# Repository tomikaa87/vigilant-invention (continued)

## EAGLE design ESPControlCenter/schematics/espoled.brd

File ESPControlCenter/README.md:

# ESP Control Center

ESP Control Center is a multifunctional unit for monitoring and interacting with
smart home equipment (like a thermostat, AC units, home server etc.).

## Hardware components

- ESP12E module [[AliExpress](https://www.aliexpress.com/item/1PCS-ESP-12F-ESP-12E-upgrade-ESP8266-Remote-Serial-Port-WIFI-Wireless-Module/32714088769.html)]
- SSD1306-based OLED display [[AliExpress](https://www.aliexpress.com/item/1pcs-Free-Shipping-White-Blue-White-and-Blue-color-0-96-inch-128X64-OLED-Display-Module/32717950155.html)]
- Push buttons
- *TODO: power supply, battery management*
 - https://www.aliexpress.com/item/DD0603SA-3V3-Auto-Buck-Boost-DC-DC-0-9-6V-to-3-3V-Step-UP-Step/32787898065.html
 - https://www.aliexpress.com/item/0-7-5V-to-3V-3-3V-5V-DC-DC-Boost-Converter-voltage-Step-up-Module/32800430445.html

## Software components

### u8g2 graphics library

#### Custom fonts from TTF

1. Download `otf2bdf` from [rtfreesoft](http://rtfreesoft.blogspot.hu/2014/12/otf2bdf-self-forked.html)
1. Download `bdfconv` from [u8g2's GitHub](https://github.com/olikraus/u8g2/blob/master/tools/font/bdfconv/bdfconv.exe)
1. (optional) Download `Chortkeh BDF Font Viewer` from [Chortkeh](http://www.chortkeh.com/font-toolbox/bdf-font-viewer) if you want to
see the contents of the generated BDF file on Windows
1. Generate a BDF file from the TTF font of your choice by running this command:
`otf2bdf.exe -r 72 -p 32 "c:\Work\ultimate_oldschool_pc_font_pack_v1.0\PxPlus (TrueType - extended charset)\PxPlus_IBM_VGA8.ttf" -o c:\Work\pxplus-vga8-32.bdf`
1. (optional) Check the result with `Chortkeh BDF Font Viewer` and see the character codes you want to encode in the next step
1. Convert the BDF file to u8g2's binary format via `bdfconv.exe -v -f 1 -m "32,48-57" ..\pxplus-vga8-32.bdf -o ..\pxplus-vga8-32.c -n pxplus_vga8_32_nums -d ..\pxplus-vga8-32.bdf`

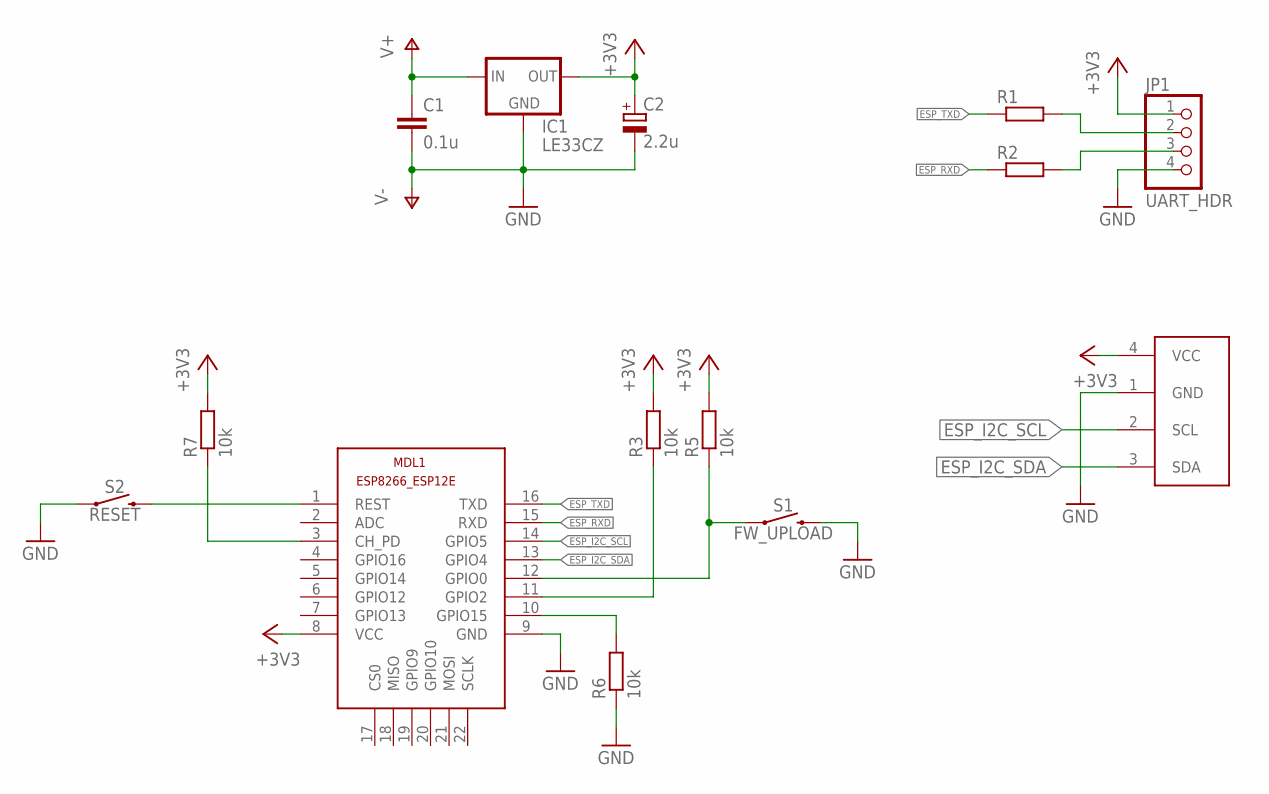
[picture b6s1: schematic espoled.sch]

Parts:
C1: 0.1u; C025-024X044
C2: 2.2u; E2,5-5
IC1: LE33CZ; TO92
JP1: UART_HDR; 1X04
MDL1: ESP8266-12EESP8266-ESP12E; ESP8266-ESP12E
OLED: I2C_OLED; I2C_OLED_PACKAGE
R1, R2: R-EU_0204/5; 0204/5
R3, R5, R6, R7: 10k; 0204/5
S1: FW_UPLOAD; TACTILE_SWITCH_PTH_6.0MM
S2: RESET; TACTILE_SWITCH_PTH_6.0MM

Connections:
+3V3: C2.+, IC1.OUT, JP1.1, MDL1.8 (VCC), OLED.4 (VCC), R3.2, R5.2, R7.2
ESP_I2C_SCL: MDL1.14 (GPIO5), OLED.2 (SCL)
ESP_I2C_SDA: MDL1.13 (GPIO4), OLED.3 (SDA)
ESP_RXD: MDL1.15 (RXD), R2.1
ESP_TXD: MDL1.16 (TXD), R1.1
GND: C1.2, C2.-, IC1.GND, JP1.4, MDL1.9 (GND), OLED.1 (GND), R6.1, S1.3 (2), S2.1
unnamed: JP1.3, R2.2
unnamed: JP1.2, R1.2
unnamed: MDL1.12 (GPIO0), R5.1, S1.1
unnamed: MDL1.1 (REST), S2.3 (2)
unnamed: MDL1.11 (GPIO2), R3.1
unnamed: MDL1.10 (GPIO15), R6.2
unnamed: MDL1.3 (CH_PD), R7.1
V+: C1.1, IC1.IN

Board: 2 copper layers, 14 parts (0 on the bottom side), 14 nets, no tracks yet.

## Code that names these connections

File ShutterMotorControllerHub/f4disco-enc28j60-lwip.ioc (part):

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Mcu.Name=STM32F407V(E-G)Tx
Mcu.Package=LQFP100
Mcu.UserName=STM32F407VGTx
PA0-WKUP.Mode=Asynchronous
PA0-WKUP.Signal=UART4_TX
PA1.Mode=Asynchronous
PA1.Signal=UART4_RX
PA10.GPIOParameters=GPIO_Speed,GPIO_PuPd,GPIO_Label,GPIO_Mode
PA10.GPIO_Label=OTG_FS_ID
PA10.GPIO_Mode=GPIO_MODE_AF_PP
PA10.GPIO_PuPd=GPIO_NOPULL
PA10.GPIO_Speed=GPIO_SPEED_FREQ_LOW
PA10.Signal=USB_OTG_FS_ID
PA11.GPIOParameters=GPIO_Speed,GPIO_PuPd,GPIO_Label,GPIO_Mode
PA11.GPIO_Label=OTG_FS_DM
PA11.GPIO_Mode=GPIO_MODE_AF_PP
PA11.GPIO_PuPd=GPIO_NOPULL
PA11.GPIO_Speed=GPIO_SPEED_FREQ_LOW
PA11.Mode=Host_Only
PA11.Signal=USB_OTG_FS_DM
PA12.GPIOParameters=GPIO_Speed,GPIO_PuPd,GPIO_Label,GPIO_Mode
PA12.GPIO_Label=OTG_FS_DP
PA12.GPIO_Mode=GPIO_MODE_AF_PP
PA12.GPIO_PuPd=GPIO_NOPULL
PA12.GPIO_Speed=GPIO_SPEED_FREQ_LOW
PA12.Mode=Host_Only
PA12.Signal=USB_OTG_FS_DP
PA13.GPIOParameters=GPIO_Label
PA13.GPIO_Label=SWDIO
PA13.Mode=Serial_Wire
PA13.Signal=SYS_JTMS-SWDIO
PA14.GPIOParameters=GPIO_Label
PA14.GPIO_Label=SWCLK
PA14.Mode=Serial_Wire
PA14.Signal=SYS_JTCK-SWCLK
PA4.GPIOParameters=GPIO_Speed,GPIO_PuPd,GPIO_Label,GPIO_Mode
PA4.GPIO_Label=I2S3_WS [CS43L22_LRCK]
PA4.GPIO_Mode=GPIO_MODE_AF_PP
PA4.GPIO_PuPd=GPIO_NOPULL
PA4.GPIO_Speed=GPIO_SPEED_FREQ_LOW
PA4.Signal=I2S3_WS
PA5.GPIOParameters=GPIO_Speed,GPIO_PuPd,GPIO_Label,GPIO_Mode
PA5.GPIO_Label=SPI1_SCK [LIS302DL_SCL/SPC]
PA5.GPIO_Mode=GPIO_MODE_AF_PP
PA5.GPIO_PuPd=GPIO_NOPULL
PA5.GPIO_Speed=GPIO_SPEED_FREQ_LOW
PA5.Mode=Full_Duplex_Master
PA5.Signal=SPI1_SCK
PA6.GPIOParameters=GPIO_Speed,GPIO_PuPd,GPIO_Label,GPIO_Mode
PA6.GPIO_Label=SPI1_MISO [LIS302DL_SDO]
PA6.GPIO_Mode=GPIO_MODE_AF_PP
PA6.GPIO_PuPd=GPIO_NOPULL
PA6.GPIO_Speed=GPIO_SPEED_FREQ_LOW
PA6.Mode=Full_Duplex_Master
PA6.Signal=SPI1_MISO
PA7.GPIOParameters=GPIO_Speed,GPIO_PuPd,GPIO_Label,GPIO_Mode
PA7.GPIO_Label=SPI1_MOSI [LIS302DL_SDA/SDI/SDO]
PA7.GPIO_Mode=GPIO_MODE_AF_PP
PA7.GPIO_PuPd=GPIO_NOPULL
PA7.GPIO_Speed=GPIO_SPEED_FREQ_LOW
PA7.Mode=Full_Duplex_Master
PA7.Signal=SPI1_MOSI
PA9.GPIOParameters=GPIO_PuPd,GPIO_Label,GPIO_Mode
PA9.GPIO_Label=VBUS_FS
PA9.GPIO_Mode=GPIO_MODE_INPUT
PA9.GPIO_PuPd=GPIO_NOPULL
PA9.Mode=Activate_VBUS
PA9.Signal=USB_OTG_FS_VBUS
PB0.GPIOParameters=GPIO_Label
PB0.GPIO_Label=NRF_CE
PB0.Signal=GPIO_Output
PB1.GPIOParameters=GPIO_Label
PB1.GPIO_Label=NRF_CSN
PB1.Signal=GPIO_Output
PB10.GPIOParameters=GPIO_Speed,GPIO_PuPd,GPIO_Label,GPIO_Mode
PB10.GPIO_Label=CLK_IN [MP45DT02_CLK]
PB10.GPIO_Mode=GPIO_MODE_AF_PP
PB10.GPIO_PuPd=GPIO_NOPULL
PB10.GPIO_Speed=GPIO_SPEED_FREQ_LOW
PB10.Signal=I2S2_CK
PB13.GPIOParameters=GPIO_Label
PB13.GPIO_Label=ENC_SCK
PB13.Mode=Full_Duplex_Master
PB13.Signal=SPI2_SCK
PB14.GPIOParameters=GPIO_Label
PB14.GPIO_Label=ENC_MISO
PB14.Mode=Full_Duplex_Master
PB14.Signal=SPI2_MISO
PB15.GPIOParameters=GPIO_Label
PB15.GPIO_Label=ENC_MOSI
PB15.Mode=Full_Duplex_Master
PB15.Signal=SPI2_MOSI
PB2.GPIOParameters=GPIO_PuPd,GPIO_Label,GPIO_Mode
PB2.GPIO_Label=BOOT1
PB2.GPIO_Mode=GPIO_MODE_INPUT
PB2.GPIO_PuPd=GPIO_NOPULL
PB2.Signal=GPIO_Input
PB3.GPIOParameters=GPIO_Label
PB3.GPIO_Label=NRF_SCK
PB3.Mode=Full_Duplex_Master
PB3.Signal=SPI3_SCK
PB4.GPIOParameters=GPIO_Label
PB4.GPIO_Label=NRF_MISO
PB4.Mode=Full_Duplex_Master
PB4.Signal=SPI3_MISO
PB5.GPIOParameters=GPIO_Label
PB5.GPIO_Label=NRF_MOSI
PB5.Mode=Full_Duplex_Master
PB5.Signal=SPI3_MOSI
PB6.GPIOParameters=GPIO_Speed,GPIO_PuPd,GPIO_Label,GPIO_Mode
PB6.GPIO_Label=Audio_SCL [CS43L22_SCL]
PB6.GPIO_Mode=GPIO_MODE_AF_OD
PB6.GPIO_PuPd=GPIO_NOPULL
PB6.GPIO_Speed=GPIO_SPEED_FREQ_LOW
PB6.Mode=I2C
PB6.Signal=I2C1_SCL
PB7.GPIOParameters=GPIO_Label
PB7.GPIO_Label=ENC_nCS
PB7.Signal=GPIO_Output
PB8.GPIOParameters=GPIO_Label
PB8.GPIO_Label=ENC_nRESET
PB8.Signal=GPIO_Output
PB9.GPIOParameters=GPIO_Speed,GPIO_PuPd,GPIO_Label,GPIO_Mode
PB9.GPIO_Label=Audio_SDA [CS43L22_SDA]
PB9.GPIO_Mode=GPIO_MODE_AF_OD
PB9.GPIO_PuPd=GPIO_NOPULL
PB9.GPIO_Speed=GPIO_SPEED_FREQ_LOW
PB9.Mode=I2C
PB9.Signal=I2C1_SDA
PC0.GPIOParameters=GPIO_Speed,PinState,GPIO_PuPd,GPIO_Label
PC0.GPIO_Label=OTG_FS_PowerSwitchOn
PC0.GPIO_PuPd=GPIO_NOPULL
PC0.GPIO_Speed=GPIO_SPEED_FREQ_LOW
PC0.PinState=GPIO_PIN_SET
PC0.Signal=GPIO_Output
PC1.GPIOParameters=GPIO_PuPd,GPIO_Label,GPIO_ModeDefaultEXTI
PC1.GPIO_Label=ENC_nIRQ
PC1.GPIO_ModeDefaultEXTI=GPIO_MODE_IT_FALLING
PC1.GPIO_PuPd=GPIO_PULLUP
PC1.Signal=GPXTI1
PC14-OSC32_IN.GPIOParameters=GPIO_Label
PC14-OSC32_IN.GPIO_Label=PC14-OSC32_IN
PC14-OSC32_IN.Mode=LSE-External-Oscillator
PC14-OSC32_IN.Signal=RCC_OSC32_IN
PC15-OSC32_OUT.GPIOParameters=GPIO_Label
PC15-OSC32_OUT.GPIO_Label=PC15-OSC32_OUT
PC15-OSC32_OUT.Mode=LSE-External-Oscillator
PC15-OSC32_OUT.Signal=RCC_OSC32_OUT
PC3.GPIOParameters=GPIO_Speed,GPIO_PuPd,GPIO_Label,GPIO_Mode
PC3.GPIO_Label=PDM_OUT [MP45DT02_DOUT]
PC3.GPIO_Mode=GPIO_MODE_AF_PP
PC3.GPIO_PuPd=GPIO_NOPULL
PC3.GPIO_Speed=GPIO_SPEED_FREQ_LOW
PC3.Signal=I2S2_SD
PC5.GPIOParameters=GPIO_Label
PC5.GPIO_Label=NRF_nIRQ
PC5.Signal=GPXTI5
PD12.GPIOParameters=GPIO_Speed,GPIO_PuPd,GPIO_Label
PD12.GPIO_Label=LD4 [Green Led]
PD12.GPIO_PuPd=GPIO_NOPULL
PD12.GPIO_Speed=GPIO_SPEED_FREQ_LOW
PD12.Signal=GPIO_Output
PD13.GPIOParameters=GPIO_Speed,GPIO_PuPd,GPIO_Label
PD13.GPIO_Label=LD3 [Orange Led]
PD13.GPIO_PuPd=GPIO_NOPULL
PD13.GPIO_Speed=GPIO_SPEED_FREQ_LOW
PD13.Signal=GPIO_Output
PD14.GPIOParameters=GPIO_Speed,GPIO_PuPd,GPIO_Label
PD14.GPIO_Label=LD5 [Red Led]
PD14.GPIO_PuPd=GPIO_NOPULL
PD14.GPIO_Speed=GPIO_SPEED_FREQ_LOW
PD14.Signal=GPIO_Output
PD15.GPIOParameters=GPIO_Speed,GPIO_PuPd,GPIO_Label
PD15.GPIO_Label=LD6 [Blue Led]
PD15.GPIO_PuPd=GPIO_NOPULL
PD15.GPIO_Speed=GPIO_SPEED_FREQ_LOW
PD15.Signal=GPIO_Output
PD4.GPIOParameters=GPIO_Speed,GPIO_PuPd,GPIO_Label
PD4.GPIO_Label=Audio_RST [CS43L22_RESET]
PD4.GPIO_PuPd=GPIO_NOPULL
PD4.GPIO_Speed=GPIO_SPEED_FREQ_LOW
PD4.Signal=GPIO_Output
PD5.GPIOParameters=GPIO_PuPd,GPIO_Label,GPIO_Mode
PD5.GPIO_Label=OTG_FS_OverCurrent
PD5.GPIO_Mode=GPIO_MODE_INPUT
PD5.GPIO_PuPd=GPIO_NOPULL
PD5.Signal=GPIO_Input
PE3.GPIOParameters=GPIO_Speed,GPIO_PuPd,GPIO_Label
PE3.GPIO_Label=CS_I2C/SPI [LIS302DL_CS_I2C/SPI]
PE3.GPIO_PuPd=GPIO_NOPULL
PE3.GPIO_Speed=GPIO_SPEED_FREQ_LOW
PE3.Signal=GPIO_Output
PH0-OSC_IN.GPIOParameters=GPIO_Label
PH0-OSC_IN.GPIO_Label=PH0-OSC_IN
PH0-OSC_IN.Mode=HSE-External-Oscillator
PH0-OSC_IN.Signal=RCC_OSC_IN
PH1-OSC_OUT.GPIOParameters=GPIO_Label
PH1-OSC_OUT.GPIO_Label=PH1-OSC_OUT
PH1-OSC_OUT.Mode=HSE-External-Oscillator
PH1-OSC_OUT.Signal=RCC_OSC_OUT
RCC.HSE_VALUE=8000000
RCC.SYSCLKFreq_VALUE=168000000
RCC.SYSCLKSource=RCC_SYSCLKSOURCE_PLLCLK
board=STM32F4DISCOVERY
boardIOC=true

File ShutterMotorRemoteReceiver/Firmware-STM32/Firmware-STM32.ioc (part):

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Mcu.Name=STM32F030K6Tx
Mcu.Package=LQFP32
Mcu.UserName=STM32F030K6Tx
PA13.Mode=Serial_Wire
PA13.Signal=SYS_SWDIO
PA14.Mode=Serial_Wire
PA14.Signal=SYS_SWCLK
PA2.Mode=Asynchronous
PA2.Signal=USART1_TX
PA3.Mode=Asynchronous
PA3.Signal=USART1_RX
PA5.GPIOParameters=GPIO_Label
PA5.GPIO_Label=SPI1_SCK
PA5.Mode=Full_Duplex_Master
PA5.Signal=SPI1_SCK
PA6.GPIOParameters=GPIO_Label
PA6.GPIO_Label=SPI1_MISO
PA6.Mode=Full_Duplex_Master
PA6.Signal=SPI1_MISO
PA7.GPIOParameters=GPIO_Label
PA7.GPIO_Label=SPI1_MOSI
PA7.Mode=Full_Duplex_Master
PA7.Signal=SPI1_MOSI
PA8.GPIOParameters=GPIO_PuPd,GPIO_Label
PA8.GPIO_Label=NRF_IRQ
PA8.GPIO_PuPd=GPIO_PULLUP
PA8.Signal=GPIO_Input
PB0.GPIOParameters=GPIO_Speed,PinState,GPIO_PuPd,GPIO_Label,GPIO_ModeDefaultOutputPP
PB0.GPIO_Label=NRF_CE
PB0.GPIO_ModeDefaultOutputPP=GPIO_MODE_OUTPUT_PP
PB0.GPIO_PuPd=GPIO_NOPULL
PB0.GPIO_Speed=GPIO_SPEED_FREQ_LOW
PB0.PinState=GPIO_PIN_RESET
PB0.Signal=GPIO_Output
PB1.GPIOParameters=GPIO_Speed,PinState,GPIO_PuPd,GPIO_Label,GPIO_ModeDefaultOutputPP
PB1.GPIO_Label=NRF_CSN
PB1.GPIO_ModeDefaultOutputPP=GPIO_MODE_OUTPUT_PP
PB1.GPIO_PuPd=GPIO_NOPULL
PB1.GPIO_Speed=GPIO_SPEED_FREQ_LOW
PB1.PinState=GPIO_PIN_RESET
PB1.Signal=GPIO_Output
PB4.GPIOParameters=GPIO_Speed,PinState,GPIO_PuPd,GPIO_Label,GPIO_ModeDefaultOutputPP
PB4.GPIO_Label=OPTO_PORT_A
PB4.GPIO_ModeDefaultOutputPP=GPIO_MODE_OUTPUT_PP
PB4.GPIO_PuPd=GPIO_NOPULL
PB4.GPIO_Speed=GPIO_SPEED_FREQ_LOW
PB4.PinState=GPIO_PIN_RESET
PB4.Signal=GPIO_Output
PB5.GPIOParameters=GPIO_Speed,PinState,GPIO_PuPd,GPIO_Label,GPIO_ModeDefaultOutputPP
PB5.GPIO_Label=OPTO_PORT_B
PB5.GPIO_ModeDefaultOutputPP=GPIO_MODE_OUTPUT_PP
PB5.GPIO_PuPd=GPIO_NOPULL
PB5.GPIO_Speed=GPIO_SPEED_FREQ_LOW
PB5.PinState=GPIO_PIN_RESET
PB5.Signal=GPIO_Output
PB6.GPIOParameters=GPIO_Speed,GPIO_FM6,PinState,GPIO_PuPd,GPIO_Label,GPIO_ModeDefaultOutputPP
PB6.GPIO_FM6=__NULL
PB6.GPIO_Label=OPTO_PORT_C
PB6.GPIO_ModeDefaultOutputPP=GPIO_MODE_OUTPUT_PP
PB6.GPIO_PuPd=GPIO_NOPULL
PB6.GPIO_Speed=GPIO_SPEED_FREQ_LOW
PB6.PinState=GPIO_PIN_RESET
PB6.Signal=GPIO_Output
PB7.GPIOParameters=GPIO_Speed,PinState,GPIO_PuPd,GPIO_Label,GPIO_ModeDefaultOutputPP,GPIO_FM7
PB7.GPIO_FM7=__NULL
PB7.GPIO_Label=OPTO_PORT_D
PB7.GPIO_ModeDefaultOutputPP=GPIO_MODE_OUTPUT_PP
PB7.GPIO_PuPd=GPIO_NOPULL
PB7.GPIO_Speed=GPIO_SPEED_FREQ_LOW
PB7.PinState=GPIO_PIN_RESET
PB7.Signal=GPIO_Output
RCC.SYSCLKFreq_VALUE=48000000
RCC.SYSCLKSource=RCC_SYSCLKSOURCE_PLLCLK
board=Firmware-STM32

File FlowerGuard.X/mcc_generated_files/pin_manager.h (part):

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// get/set channel_AN2 aliases
#define channel_AN2_TRIS                 TRISAbits.TRISA2
#define channel_AN2_LAT                  LATAbits.LATA2
#define channel_AN2_PORT                 PORTAbits.RA2
#define channel_AN2_WPU                  WPUAbits.WPUA2
#define channel_AN2_ANS                  ANSELAbits.ANSA2
#define channel_AN2_SetHigh()            do { LATAbits.LATA2 = 1; } while(0)
#define channel_AN2_SetLow()             do { LATAbits.LATA2 = 0; } while(0)
#define channel_AN2_Toggle()             do { LATAbits.LATA2 = ~LATAbits.LATA2; } while(0)
#define channel_AN2_GetValue()           PORTAbits.RA2
#define channel_AN2_SetDigitalInput()    do { TRISAbits.TRISA2 = 1; } while(0)
#define channel_AN2_SetDigitalOutput()   do { TRISAbits.TRISA2 = 0; } while(0)
#define channel_AN2_SetPullup()          do { WPUAbits.WPUA2 = 1; } while(0)
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// get/set IO_SENSOR_PWR aliases
#define IO_SENSOR_PWR_TRIS                 TRISAbits.TRISA4
#define IO_SENSOR_PWR_LAT                  LATAbits.LATA4
#define IO_SENSOR_PWR_PORT                 PORTAbits.RA4
#define IO_SENSOR_PWR_WPU                  WPUAbits.WPUA4
#define IO_SENSOR_PWR_ANS                  ANSELAbits.ANSA4
#define IO_SENSOR_PWR_SetHigh()            do { LATAbits.LATA4 = 1; } while(0)
#define IO_SENSOR_PWR_SetLow()             do { LATAbits.LATA4 = 0; } while(0)
#define IO_SENSOR_PWR_Toggle()             do { LATAbits.LATA4 = ~LATAbits.LATA4; } while(0)
#define IO_SENSOR_PWR_GetValue()           PORTAbits.RA4
#define IO_SENSOR_PWR_SetDigitalInput()    do { TRISAbits.TRISA4 = 1; } while(0)
#define IO_SENSOR_PWR_SetDigitalOutput()   do { TRISAbits.TRISA4 = 0; } while(0)
#define IO_SENSOR_PWR_SetPullup()          do { WPUAbits.WPUA4 = 1; } while(0)
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// get/set SCL aliases
#define SCL_TRIS                 TRISCbits.TRISC0
#define SCL_LAT                  LATCbits.LATC0
#define SCL_PORT                 PORTCbits.RC0
#define SCL_WPU                  WPUCbits.WPUC0
#define SCL_ANS                  ANSELCbits.ANSC0
#define SCL_SetHigh()            do { LATCbits.LATC0 = 1; } while(0)
#define SCL_SetLow()             do { LATCbits.LATC0 = 0; } while(0)
#define SCL_Toggle()             do { LATCbits.LATC0 = ~LATCbits.LATC0; } while(0)
#define SCL_GetValue()           PORTCbits.RC0
#define SCL_SetDigitalInput()    do { TRISCbits.TRISC0 = 1; } while(0)
#define SCL_SetDigitalOutput()   do { TRISCbits.TRISC0 = 0; } while(0)
#define SCL_SetPullup()          do { WPUCbits.WPUC0 = 1; } while(0)
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// get/set SDA aliases
#define SDA_TRIS                 TRISCbits.TRISC1
#define SDA_LAT                  LATCbits.LATC1
#define SDA_PORT                 PORTCbits.RC1
#define SDA_WPU                  WPUCbits.WPUC1
#define SDA_ANS                  ANSELCbits.ANSC1
#define SDA_SetHigh()            do { LATCbits.LATC1 = 1; } while(0)
#define SDA_SetLow()             do { LATCbits.LATC1 = 0; } while(0)
#define SDA_Toggle()             do { LATCbits.LATC1 = ~LATCbits.LATC1; } while(0)
#define SDA_GetValue()           PORTCbits.RC1
#define SDA_SetDigitalInput()    do { TRISCbits.TRISC1 = 1; } while(0)
#define SDA_SetDigitalOutput()   do { TRISCbits.TRISC1 = 0; } while(0)
#define SDA_SetPullup()          do { WPUCbits.WPUC1 = 1; } while(0)
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// get/set SDO aliases
#define SDO_TRIS                 TRISCbits.TRISC2
#define SDO_LAT                  LATCbits.LATC2
#define SDO_PORT                 PORTCbits.RC2
#define SDO_WPU                  WPUCbits.WPUC2
#define SDO_ANS                  ANSELCbits.ANSC2
#define SDO_SetHigh()            do { LATCbits.LATC2 = 1; } while(0)
#define SDO_SetLow()             do { LATCbits.LATC2 = 0; } while(0)
#define SDO_Toggle()             do { LATCbits.LATC2 = ~LATCbits.LATC2; } while(0)
#define SDO_GetValue()           PORTCbits.RC2
#define SDO_SetDigitalInput()    do { TRISCbits.TRISC2 = 1; } while(0)
#define SDO_SetDigitalOutput()   do { TRISCbits.TRISC2 = 0; } while(0)
#define SDO_SetPullup()          do { WPUCbits.WPUC2 = 1; } while(0)
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#define RC5_SetHigh()            do { LATCbits.LATC5 = 1; } while(0)
#define RC5_SetLow()             do { LATCbits.LATC5 = 0; } while(0)
#define RC5_Toggle()             do { LATCbits.LATC5 = ~LATCbits.LATC5; } while(0)
#define RC5_GetValue()              PORTCbits.RC5
#define RC5_SetDigitalInput()    do { TRISCbits.TRISC5 = 1; } while(0)
#define RC5_SetDigitalOutput()   do { TRISCbits.TRISC5 = 0; } while(0)
#define RC5_SetPullup()             do { WPUCbits.WPUC5 = 1; } while(0)
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
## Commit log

2018-01-08 Add ESPControlCenter
2018-01-29 Add ShutterMotorController
2018-01-29 SMC: fix screw terminal pin pitch; route +3.3V to DS18B20 differently
2018-02-03 ESPControlCenter: add RPi playground project
2018-02-03 ESPControlCenter playground: move sources to src
2018-02-03 ESPControlCenter: add more characters to PxPlus VGA8 32px; update playground
2018-02-03 ESPControlCenter: add crypto, drivers, ui
2018-02-03 Update gitignore
2018-02-03 ESPControlCenter: add NAS status screen to Playground
2018-02-03 ESPControlCenter-Playground: move screens to a separate folder
2018-02-03 ESPControlCenter-Playground: initial commit of air conditioner screen
2018-02-03 ESPControlCenter-Playground: implement AC fan speed indicator
2018-02-11 SMC: add indicator LED
2018-02-11 SMC: initial commit of the Firmware
2018-02-12 SMC: initial commit of BlynkHandler and RelayController
2018-02-12 SMC: handle Blynk button presses
2018-02-12 SMC: add ADC header to the PCB
2018-02-13 SMC: implement relay grouping in RelayController
2018-02-13 SMC: do some cosmetic changes
2018-02-13 SMC: add Clock module with NTP support
2018-02-16 SMC: fix DRC errors of board design
2018-02-18 SMC: fix screw-terminal pin pitch and drawing
2018-02-18 SMC: increase clearance between switched relay tracks
2018-02-18 SMC: increase annular ring size of screw terminals
2018-02-20 SMC: use const-correct version of NTPClient
2018-02-25 SMC: implement persistent config and automation timer
2018-02-28 SMC: implement a more clever logging mechanism
2018-02-28 SMC: fix logger prefixes; add some more logging; don't log to Blynk while it's disconnected
2018-02-28 SMC: create README.md
2018-03-18 Add Eagle libraries used by the sub-projects
2018-03-18 ShutterMotorRemoteReceiver: initial commit
2018-06-26 SMCH: add stm32f4discovery prototype project
2018-06-26 SMCH: move prototype project to a separate folder
2018-06-26 SMCH: add SMRHubTest prototype project
2018-06-26 SMRR: add STM32F103 (MX) prototype project
2018-06-26 SMCH: update SMRHubTest
2018-06-26 SMCH: disable USB host code, move lwIP buffers to CCMRAM
2018-06-27 SMCH: convert proto to a C++ project
2018-06-27 SMCH: format and clean-up proto code
2018-06-27 SMCH: initial commit of proto TestSocket
2018-06-30 SMCH: implement basic TCP communication in the proto
2018-07-01 SMCH: initial commit of Blynk in proto
2018-07-03 SMCH: initial commit of a very basic Qt implementation
2018-08-04 Shutter Motor Remote Receiver: inital commit
2018-08-18 SMC: fix DST handling
2018-08-18 SMRR: reset PLOS_CNT when it reaches 15
2018-08-19 SMCH: reset PLOS_CNT when it reaches 15
2018-08-19 SMCH: reset PLOS_CNT on mode switch; clean up the code
2018-08-19 SMRR: reset PLOS_CNT on switching mode
2018-08-19 SMCH: show "scan" and "read status" output on Diag Terminal
2018-08-20 SMCH: initial commit of new interfaces
2018-08-21 SMCH: initial commit of new Hub implementation
2018-09-13 SMRR: increase RF output power to 0 dbm
2018-09-13 SMCH: attempt to avoid stuck state
2018-09-19 SMCH: fix compilation errors with non-MSVC compilers
2018-09-24 SMCH: add kitchen shutters, use step up/down widgets instead of buttons
2018-09-24 SMCH: enable debugging, fix nrf24_dump_registers
2018-10-13 Scheduling with Blynk
2018-10-13 SMCH: move files around
2018-10-13 Add Qt shadow build directories to gitignore
2018-10-13 SMCH: move git submodules under 3rdparty
2018-10-13 SMCH: fix include paths
2018-10-13 SMCH: initial commit of the future-based interface
2018-10-13 SMCH: implement logging helpers, clean up the code
2018-10-14 SMCH: implement basic hub functions with OperationQueue
2018-10-14 SMCH: clean up the code a little bit
2018-10-14 SMCH: fix device creation during scan
2018-10-16 SMCH: initial commit of new Radio
2018-10-16 SMCH: implement (almost) working Radio
2018-10-16 SMCH: add Radio implementation
2018-10-16 SMRR: implement delay before sending the response to the Hub
2018-10-16 SMRR: add extra clean up code to mode switching logic
2018-10-16 SMRR: implement ALL UP and ALL DOWN commands
2018-10-16 SMCH: tweak Radio a little bit
2018-11-10 SMCH: initial commit of new Diag Menu; enable C++17
2018-11-10 SMCH: clean up, optimizations
2018-11-10 SMCH: add device status query to Hub
2018-11-10 SMCH: implement some device functions in Diag Menu
2018-11-10 SMRR: initial commit of OpenBLT-based bootloader
2018-11-10 SMRR-BL: enable multiprocessor compilation, disable USART
2018-11-10 SMRR-BL: increase reserved flash size
2018-11-10 SMRR: reserve flash space for the bootloader
2018-11-11 SMCH: implement more detailed device info
2018-12-15 Add ChristmastLightsTimer
2018-12-15 Initial commit of ChargeController
2018-12-18 New ChargeController schematics for proto board
2018-12-31 Initial commit of TouchScreenTest
2018-12-31 TouchScreenTest: clean up TPFilter
2018-12-31 TouchScreenTest: fix the project
2018-12-31 TouchScreenTest: clean up the code
2018-12-31 TouchScreenTest: remove factory test images
2019-01-01 TouchScreenTest: implement proper 8080 parallel control; implement SetPixel via RMW
2019-01-02 TouchScreenTest: implement multi color drawing test
2019-01-05 TouchScreenTest: initial commit of simple widget support
2019-01-06 ChargeController: initial commit of Android app
2019-01-06 ChargeController: add new launcher icon
2019-01-10 TouchScreenTest: use multi channel ADC with DMA to handle the touchpad
2019-01-10 TouchScreenTest: adjust touchpad detect threshold; fix Rect
2019-01-19 ChargeController: initial commit of notification update
2019-01-19 ChargerController: migrate to AndroidX
2019-01-19 ChargeController: improve notification
2019-01-19 ChargeController: initial commit of Firmware
2019-01-19 ChargeController: update Android project
2019-01-19 ChargeController: implement power output keep-alive
2019-01-19 ChargeController: add script which starts serial monitor
2019-01-19 ChargeController: update output state on the notification properly
2019-01-19 ChargeController: notification alerts only once
2019-01-19 Update README.md
    Add ChargeController
2019-01-26 ChargeController: implement smarter LED control in the firmware
2019-01-26 ChargerController: increase keep-alive interval
2019-01-26 ChargeController: disable AP mode in ESP
2019-01-27 ChargeController: simplify the Timer
2019-01-27 ChargeController: clean-up the firmware code
2019-01-30 ShutterMotorController: use local blynk server
2019-01-30 ChargeController: greatly improve connection stability
2019-01-31 ChargeController: disable backup to avoid killing the service
2019-04-17 ChargeController: replace hardwired charging limits
2019-04-17 ChargeController: add logging
2019-04-17 ChargeController: update gradle
2019-04-18 ChargeController: re-enable output in keep-alive task after the connection is restored
2019-05-03 TeveclubAutomator: initial commit
2019-05-03 TeveclubAutomator: update QMake project
2019-05-04 TeveclubAutomator: initial commint of main page handler
2019-05-04 TeveclubAutomator: implement feeding
2019-05-04 TeveclubAutomator: implement teaching
2019-05-05 TeveclubAutomator: prepare to be used with Cron
2019-05-05 TeveclubAutomator: fix QMake project for Linux
2019-05-05 TeveclubAutomator: add check for login result
2019-05-14 TeveclubAutomator: fix stuck state when only one action is selected, rename configuration file
2019-05-14 ChargeController: use domain name instead of fix IP
2019-05-14 TeveclubAutomator: implement random skill selection from teaching page
2019-05-14 TeveclubAutomator: fix spelling error on the help screen
2019-05-15 TeveclubAutomator: implement smarter state/action handling
2019-05-15 TeveclubAutomator: implement proper teaching form handling
2019-05-15 TeveclubAutomator: implement playing with the Wonderful One Number game
2019-08-16 ChristmasLightsTimer: implement ON period setting
2019-08-17 ChristmasLightsTimer: improve button handling, clean-up the code
2019-08-17 ChristmasLightsTimer: optimize the code
2019-08-17 ChristmasLightsTimer: clarify the code a little bit
2019-08-17 ChristmasLightsTimer: fix minor issues
2019-12-31 Add FlowerGuard flower watering alarm
2020-11-07 SMRR: add test project for ST32F103
2021-09-02 CLT: implementation for 12F1840, add tuning options to 12F683
2021-09-02 CLT: add schematics and PCB design with 12F1840
2022-01-13 Add pico-snowfall
2022-01-13 Add pico-oled-widgets
2022-01-13 Add pico-bufferless-oled
2022-01-14 Add ChristmasLightsTimer v2
2022-01-15 pico-oled-widgets: fix text drawing
2022-01-15 pico-oled-widgets: implement simple text clipping
2022-11-26 pico-snowfall: add battery voltage measurement
2023-01-08 pic-snowfall: initial commit
2023-01-08 pic-snowfall: reduce memory usage of snow pile heights structure
2023-01-08 pic-snowfall: clean up the code
2023-01-08 pic-snowfall: prepare the code for the buffer-less implementation
2023-01-08 pic-snowfall: implement bufferless drawing (very slow at the moment)
2023-01-08 pic-snowfall: optimize a bit
2023-01-09 pic-snowfall: optimize speed of bufferless drawing
